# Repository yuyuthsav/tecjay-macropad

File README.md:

# tecjay-macropad
A macropad with hot-swap sockets with 9 keys and a 3*3 layout

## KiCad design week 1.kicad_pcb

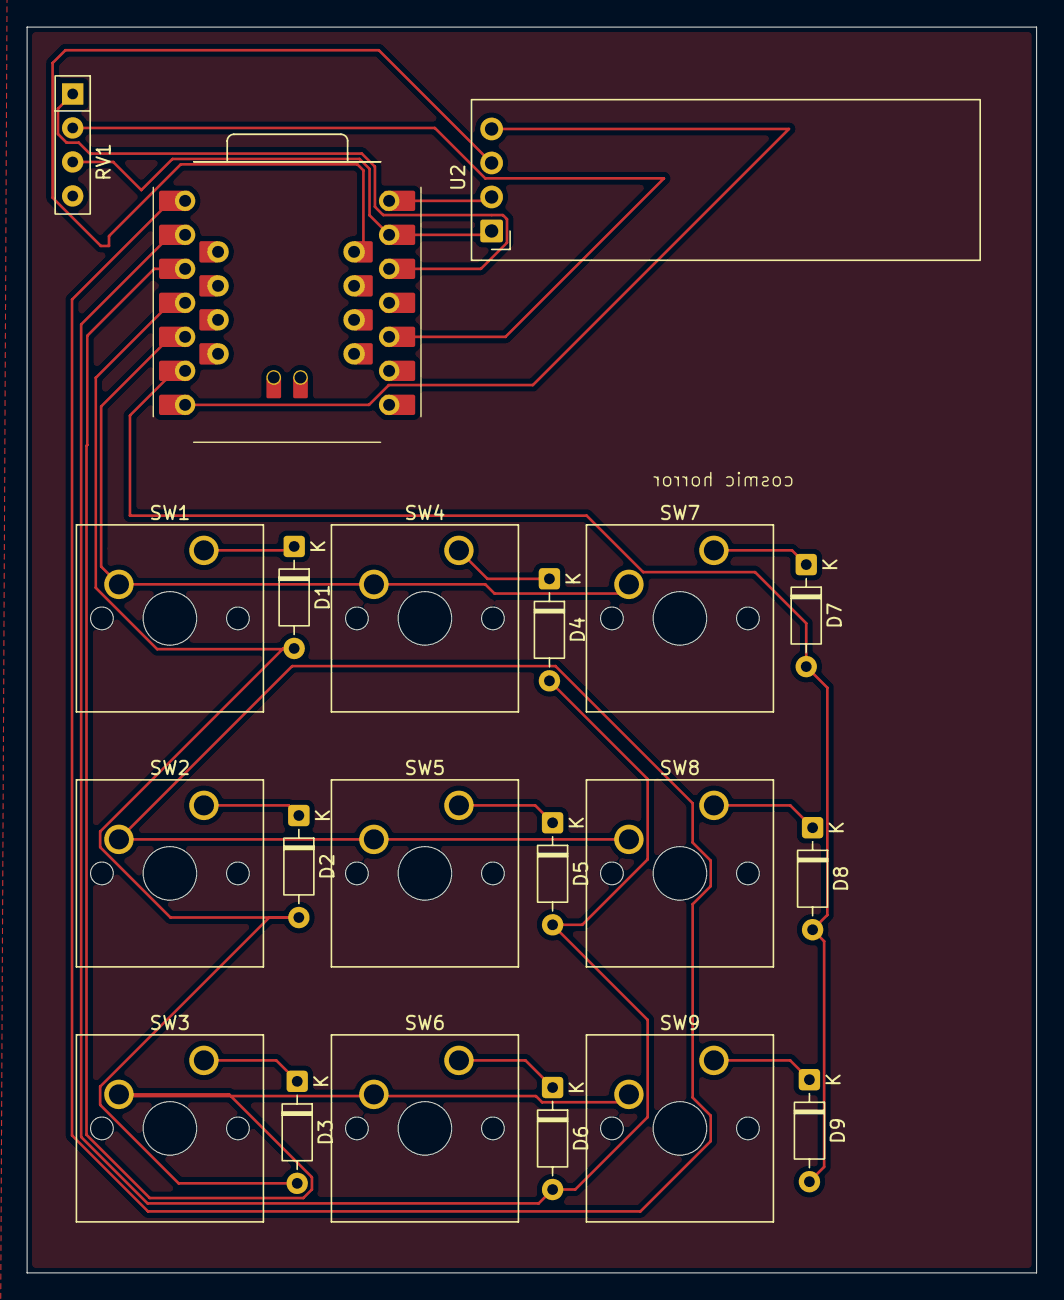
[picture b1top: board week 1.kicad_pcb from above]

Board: 2 copper layers, 75.4 x 93.1 mm, 21 parts (0 on the bottom side), 21 nets.

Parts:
D1, D2, D3, D4, D5, D6, D7, D8, D9: 1N4148; D_DO-35_SOD27_P7.62mm_Horizontal
RV1: R_Potentiometer; R_Array_SIP4
SW1, SW2, SW3, SW4, SW5, SW6, SW7, SW8, SW9: SW_Push; SW_Cherry_MX_1.00u_PCB
U1: XIAO-RP2350-DIP
U2: ER_OLEDM0.91_1x-I2C

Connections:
/COL1: D1.2 (A), D2.2 (A), D3.2 (A), U1.4 (D3)
/COL2: D4.2 (A), D5.2 (A), D6.2 (A), U1.2 (D1)
/COL3: D7.2 (A), D8.2 (A), D9.2 (A), U1.6 (D5)
/ROW1: SW1.2, SW4.2, SW7.2, U1.5 (D4)
/ROW2: SW2.2, SW5.2, SW8.2, U1.1 (D0)
/ROW3: SW3.2, SW6.2, SW9.2, U1.3 (D2)
unnamed: D1.1 (K), SW1.1
unnamed: D2.1 (K), SW2.1
unnamed: D3.1 (K), SW3.1
unnamed: D4.1 (K), SW4.1
unnamed: D5.1 (K), SW5.1
unnamed: D6.1 (K), SW6.1
unnamed: D7.1 (K), SW7.1
unnamed: D8.1 (K), SW8.1
unnamed: D9.1 (K), SW9.1
unnamed: RV1.1, U1.12 (3V3_OUT)
unnamed: U1.7 (D6), U2.4 (SDA)
unnamed: RV1.2, U1.10 (D9)
unnamed: U1.15 (D11), U2.3 (SCL)
unnamed: U1.14 (VBUS), U2.2 (VCC)
unnamed: RV1.3, U1.13 (GND), U2.1 (GND)
